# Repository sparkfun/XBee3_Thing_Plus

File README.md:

SparkFun XBee3 Thing Plus
========================================

<table class="table table-hover table-striped table-bordered">
  <tr align="center">
   <td></td>
   <td></td>
  </tr>
  <tr align="center">
   <td><i>SparkFun XBee3 Thing Plus (u.FL) [<a href="https://www.sparkfun.com/products/15435">WRL-15435</a>]</i></td>
   <td><i>SparkFun XBee3 Thing Plus (PCB Antenna) [<a href="https://www.sparkfun.com/products/15454">WRL-15454</a>]</i></td>
  </tr>
</table>

The XBee3 Thing Plus is an ultra capable and easy way for getting into wireless device development. The combination of XBee and Qwiic in a space conscious design represents a much needed update to our XBee offering. With 20 I/O pins and Lithium Polymer Ion battery management, the XBee3 Thing Plus has all the basics for quickly prototyping or developing a connected device such as a remote sensor. The Qwiic connector and JST connector for the battery make for a solder-less option when working with the board which shortens setup time.

The new XBee3 Micro Module provides the classic all-but plug and play 802.15.4 2.4GHz wireless connection (Zigbee 3.0 Protocol) that makes it so desirable, but with a new addition of being programmable with MicroPython (32KB of memory available for it). RF data rates up to 250 Kbps and 200ft indoor ranges and up to 4000ft line-of-sight outdoor range. Communicating with/Configuring the module happens via an AT Command set or the Digi API, X-CTU, both locally or over-the-air. There's even a mobile version of X-CTU now; Digi XBee® Mobile.

This variation features a U.FL antenna connector for longer range communications.

Repository Contents
-------------------

* **/Hardware** - Eagle design files (.brd, .sch)

Documentation
--------------
* **[Hookup Guide](https://learn.sparkfun.com/tutorials/xbee3-thing-plus-hookup-guide)** - Basic hookup guide for the XBee Thing Plus.
* **[SparkFun Fritzing repo](https://github.com/sparkfun/Fritzing_Parts)** - Fritzing diagrams for SparkFun products.

License Information
-------------------

This product is _**open source**_! 

Please review the LICENSE.md file for license information. 

If you have any questions or concerns on licensing, please contact technical support on our [SparkFun forums](https://forum.sparkfun.com/viewforum.php?f=152).

Distributed as-is; no warranty is given.

- Your friends at SparkFun.

_<COLLABORATION CREDIT>_

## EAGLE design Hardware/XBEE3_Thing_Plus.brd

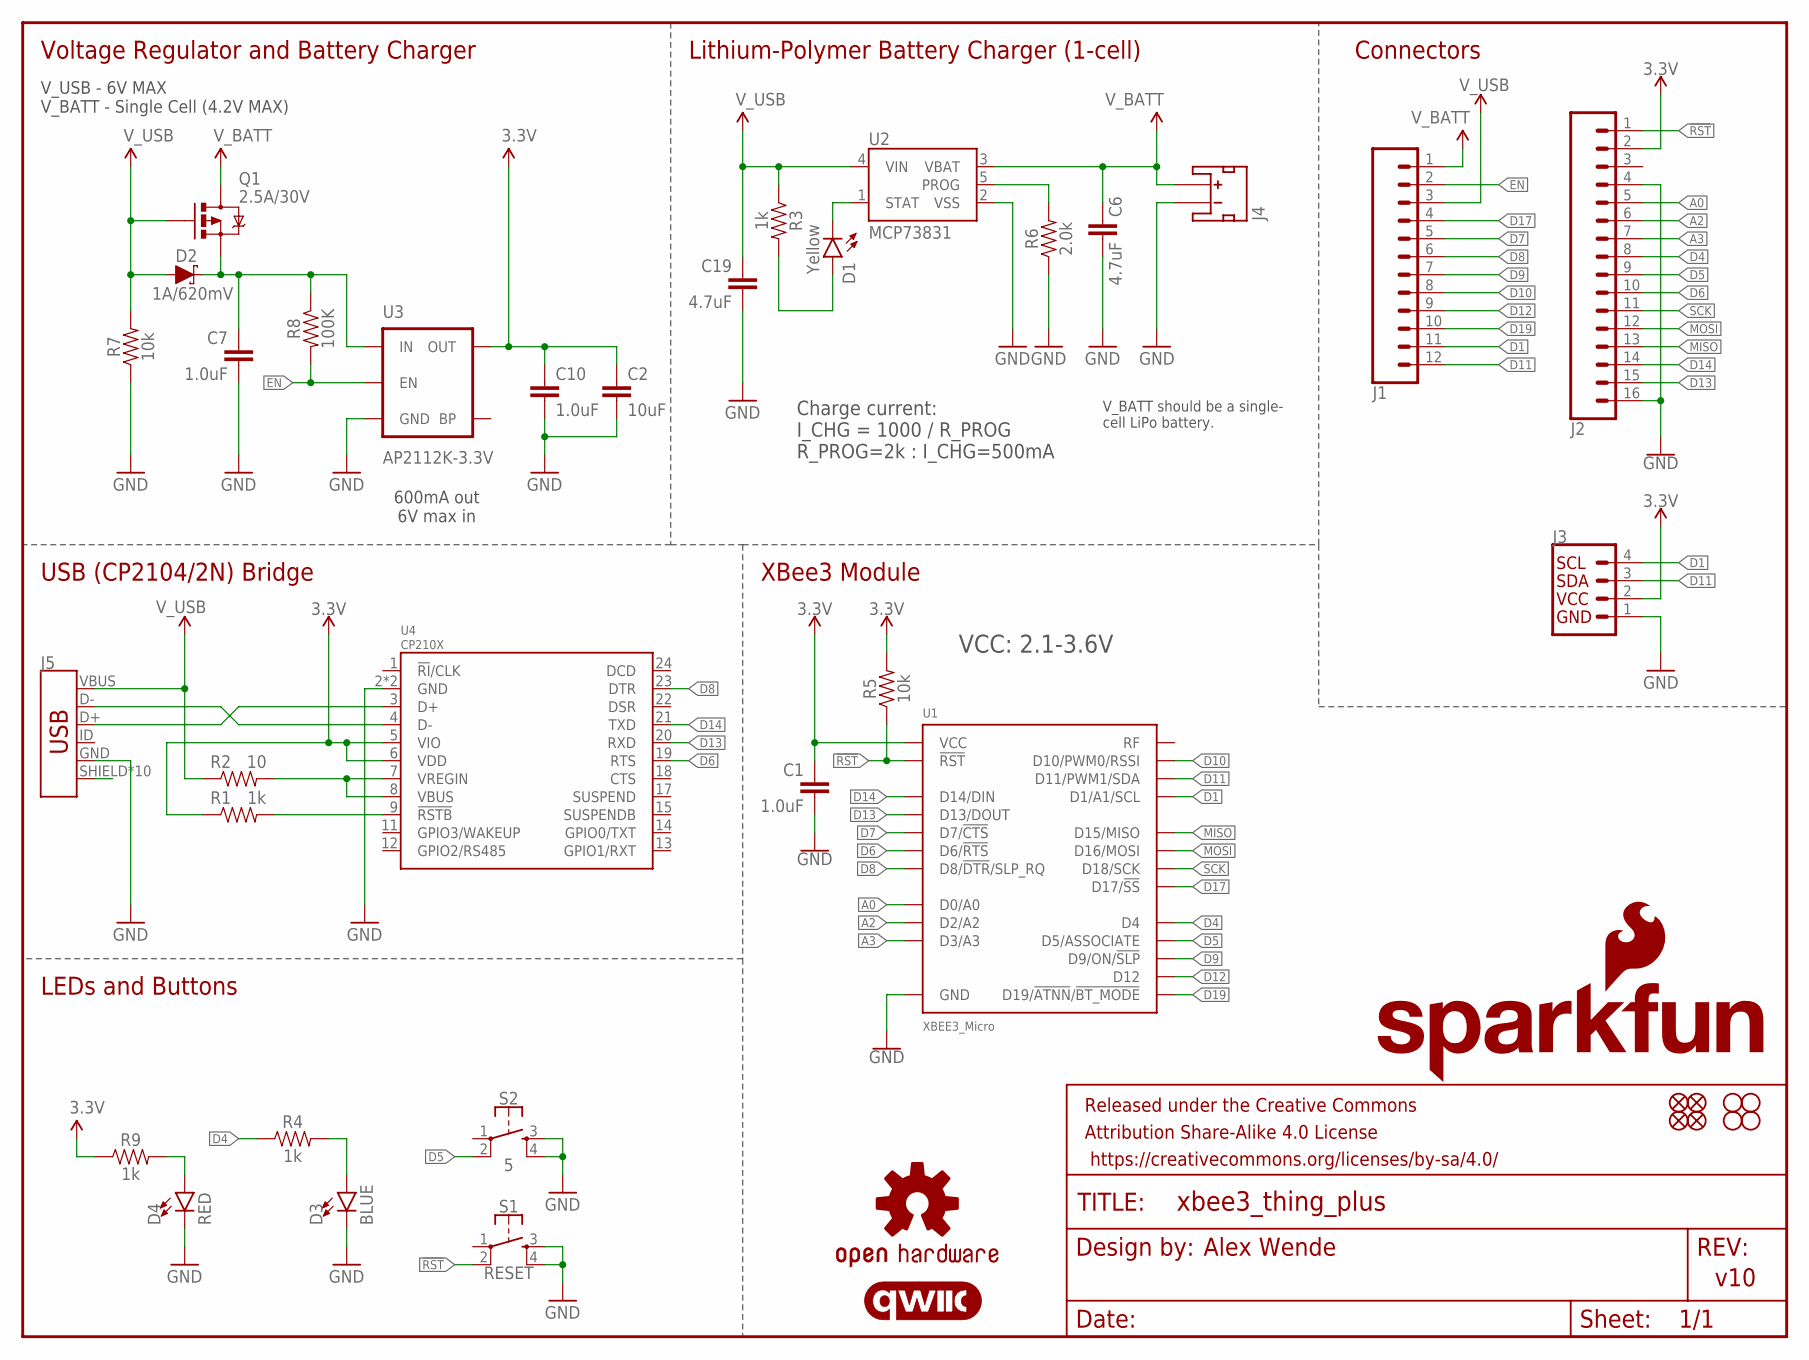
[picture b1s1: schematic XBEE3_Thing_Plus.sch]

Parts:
C1, C7: 1.0uF; 0603
C2: 10uF; 0603
C6, C19: 4.7uF; 0603
C10: 1.0uF; 0402
D1: Yellow; LED-0603
D2: 1A/620mV; SOD-323
D3: BLUE; LED-0603
D4: RED; LED-0603
FD1, FD2, FD3, FD4: FIDUCIALUFIDUCIAL; FIDUCIAL-MICRO
FRAME1: FRAME-LETTER; CREATIVE_COMMONS
H1, H2, H3, H4: STAND-OFF
J1: CONN_12SM_SQ_NO_SILK; 1X12_SM_SQ_NOSILK
J2: CONN_161X16_SM_SQ_NOSILK; 1X16_SM_SQ_NOSILK
J3: QWIIC_CONNECTORJS-1MM; JST04_1MM_RA
J4: JST_2MM_MALE; JST-2-SMD
J5: USB_MICRO-B_HALF_PTH_MILL; USB-MICROB-PTH-MILL
LOGO1: SFE_LOGO_NAME_FLAME.1_INCH; SFE_LOGO_NAME_FLAME_.1
LOGO2: OSHW-LOGOS; OSHW-LOGO-S
Q1: 2.5A/30V; SOT23-3@1
R1, R3, R4, R9: 1k; 0603
R2: 10; 0603
R5, R7: 10k; 0603
R6: 2.0k; 0603
R8: 100K; 0402
S1: RESET; TACTILE_SWITCH_SMD_4.6X2.8MM
S2: 5; TACTILE_SWITCH_SMD_4.6X2.8MM
U1: XBEE3_Micro; XBEE3
U2: MCP73831; SOT23-5
U3: AP2112K-3.3V; SOT23-5
U4: CP210X; QFN24
U$63: QWIIC_LOGO_5MM; QWIIC_5MM

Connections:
3.3V: C1.1, C2.1, C10.1, J2.2, J3.2, R1.1, R5.2, R9.1, U1.P$2 (VCC), U3.5 (OUT), U4.5 (VIO), U4.6 (VDD)
!RST: J2.1, R5.1, S1.2, U1.P$6 (!RST)
A0: J2.5, U1.P$31 (D0/A0)
A2: J2.6, U1.P$29 (D2/A2)
A3: J2.7, U1.P$28 (D3/A3)
CHG: D1.C, U2.1 (STAT)
D1: J1.11, J3.4, U1.P$30 (D1/A1/SCL)
D4: J2.8, R4.1, U1.P$23 (D4)
D5: J2.9, S2.2, U1.P$26 (D5/ASSOCIATE)
D6: J2.10, U1.P$27 (D6/!RTS), U4.19 (RTS)
D7: J1.5, U1.P$24 (D7/!CTS)
D8: J1.6, U1.P$9 (D8/!DTR!/SLP_RQ), U4.23 (DTR)
D9: J1.7, U1.P$25 (D9/ON/!SLP)
D10: J1.8, U1.P$7 (D10/PWM0/RSSI)
D11: J1.12, J3.3, U1.P$8 (D11/PWM1/SDA)
D12: J1.9, U1.P$5 (D12)
D13: J2.15, U1.P$3 (D13/DOUT), U4.20 (RXD)
D14: J2.14, U1.P$4 (D14/DIN), U4.21 (TXD)
D17: J1.4, U1.P$14 (D17/!SS)
D19: J1.10, U1.P$11 (D19/!ATNN!/!BT_MODE)
D+: J5.D+, U4.3 (D+)
D-: J5.D-, U4.4 (D-)
EN: J1.2, R8.2, U3.3 (EN)
GND: C1.2, C2.2, C6.2, C7.2, C10.2, C19.2, D3.C, D4.C, J2.4, J2.16, J3.1, J4.1 (-), J5.GND, R6.1, R7.1, S1.3, S1.4, S2.3, S2.4, U1.P$1 (GND), U1.P$10 (GND), U1.P$12 (GND), U1.P$21 (GND), U1.P$32 (GND), U1.P$34 (GND), U2.2 (VSS), U3.2 (GND), U4.2 (GND), U4.PAD (GND)
MISO: J2.13, U1.P$16 (D15/MISO)
MOSI: J2.12, U1.P$15 (D16/MOSI)
unnamed: C7.1, D2.C, Q1.2 (S), R8.1, U3.1 (IN)
unnamed: R1.2, U4.9 (!RSTB)
unnamed: R2.2, U4.7 (VREGIN), U4.8 (VBUS)
unnamed: D3.A, R4.2
unnamed: D4.A, R9.2
unnamed: J5.SHIELD, J5.SHIELD2 (SHIELD), J5.SHIELD3 (SHIELD), J5.SHIELD4 (SHIELD), J5.SHIELD5 (SHIELD), J5.SHIELD6 (SHIELD), J5.SHIELD7 (SHIELD), J5.SHIELD8 (SHIELD), J5.SHIELD9 (SHIELD), J5.SHIELD10 (SHIELD)
unnamed: R6.2, U2.5 (PROG)
unnamed: D1.A, R3.2
SCK: J2.11, U1.P$13 (D18/SCK)
V_BATT: C6.1, J1.1, J4.2 (+), Q1.3 (D), U2.3 (VBAT)
V_USB: C19.1, D2.A, J1.3, J5.VBUS, Q1.1 (G), R2.1, R3.1, R7.2, U2.4 (VIN)

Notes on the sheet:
Voltage Regulator and Battery Charger
600mA out 6V max in
V_USB - 6V MAX V_BATT - Single Cell (4.2V MAX)
V_BATT should be a single- cell LiPo battery.
Charge current: I_CHG = 1000 / R_PROG R_PROG=2k : I_CHG=500mA
Lithium-Polymer Battery Charger (1-cell)
Alex Wende
v10
USB (CP2104/2N) Bridge
Connectors
XBee3 Module
LEDs and Buttons
VCC: 2.1-3.6V

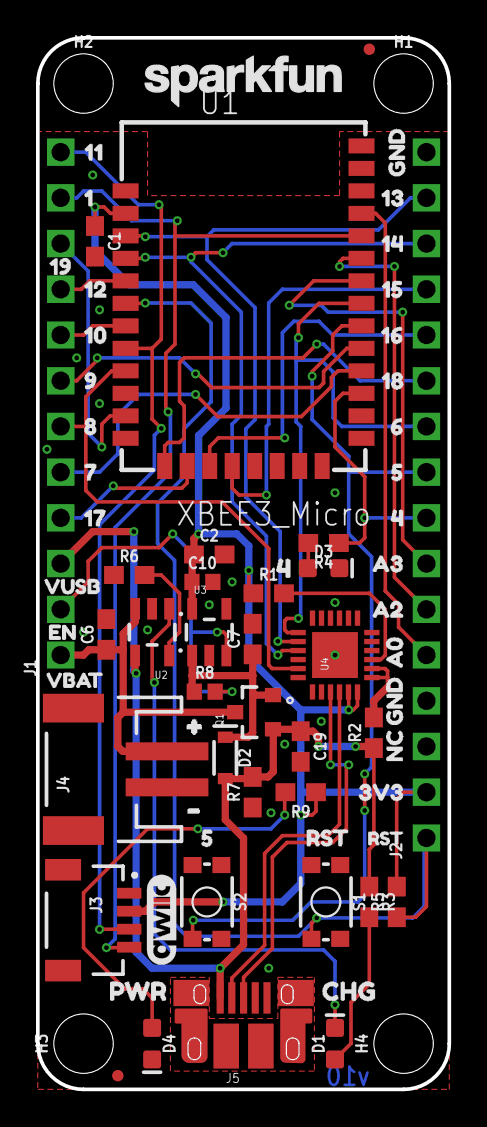
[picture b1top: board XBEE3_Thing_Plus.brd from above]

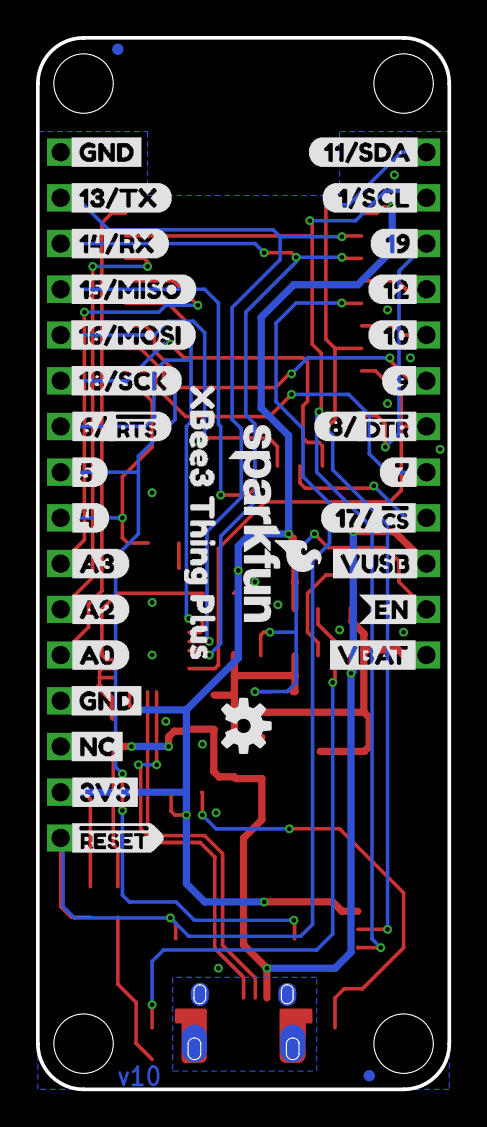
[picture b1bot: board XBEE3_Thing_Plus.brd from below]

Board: 2 copper layers, 22.9 x 58.4 mm, 111 parts (36 on the bottom side), 37 nets.

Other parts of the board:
U$1: #RESET0
U$2: 3V31
U$3: NC2
U$4, U$16: GND3
U$5: A04
U$6: A26
U$7: A35
U$8: 47
U$9: 58
U$11: 18#SCK10
U$12: 16#MOSI11
U$13: 15#MISO12
U$14: 14#RX13
U$15: 13#TX14
U$17: VBAT16
U$18: EN17
U$19: VUSB18
U$20: SFE_LOGO_NAME_.1
U$21: 719
U$23, U$50: 921
U$24: 1022
U$25: 1223
U$26: 1924
U$27: 1#SCL25
U$28: 11#SDA26
U$29: 170
U$30: 131
U$31: 142
U$32: 153
U$33: 164
U$34: 185
U$35: 66
U$36: 57
U$37: 48
U$38: A39
U$39: A210
U$40: A011
U$41, U$62: GND12
U$42: NC13
U$43: 3V314
U$44: #RST15
U$45: 1116
U$46: 117
U$47: 1918
U$48: 1219
U$49: 1020
U$51: 822
U$52: 723
U$54: VUSB4
U$55: EN3
U$56: PWR0
U$57: 51
U$58: RST0
U$59: 44
U$60: VBAT2
U$61: CHG1
U$64: #1
U$65: XBEE3_THING_PLUS0
U$66: #2
U$67: 6#0
U$68: #RTS1
U$69: #DTR3
U$70: 8#2
U$71: 17#4
U$72: #CS5

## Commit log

2019-06-11 v01 update
    Removed test points from bottom of the board, removed the trace antenna, and modified the top ground pour as outlined in the XBee3 datasheet
2019-06-12 v01 Design Review Changes
    - Adjusted R2
    - Modified bottom ground pour
    - Swapped D17 and extra ground header pads
    - Updated buzzard labels
    - Rotated name and logo on bottom
    - Added SparkFun name logo to top of board
2019-07-02 v10 design review changes
    Added input voltage range note for the XBee3 module in schematic
2019-07-02 Updated XBee3 PROD_ID
    Added the chip antenna PROD_ID along with the u.FL ID
2020-09-08 Updated USB to UART bridge
    Update schematic to use either the CP2104 or CP2102N USB to UART bridge

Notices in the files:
parts and their libraries:
SparkFun-Capacitors: Licensing: Creative Commons ShareAlike 4.0 International - https://creativecommons.org/licenses/by-sa/4.0
SparkFun-Aesthetics: Released under the Creative Commons Attribution Share-Alike 4.0 License
SparkFun-Aesthetics: https://creativecommons.org/licenses/by-sa/4.0
